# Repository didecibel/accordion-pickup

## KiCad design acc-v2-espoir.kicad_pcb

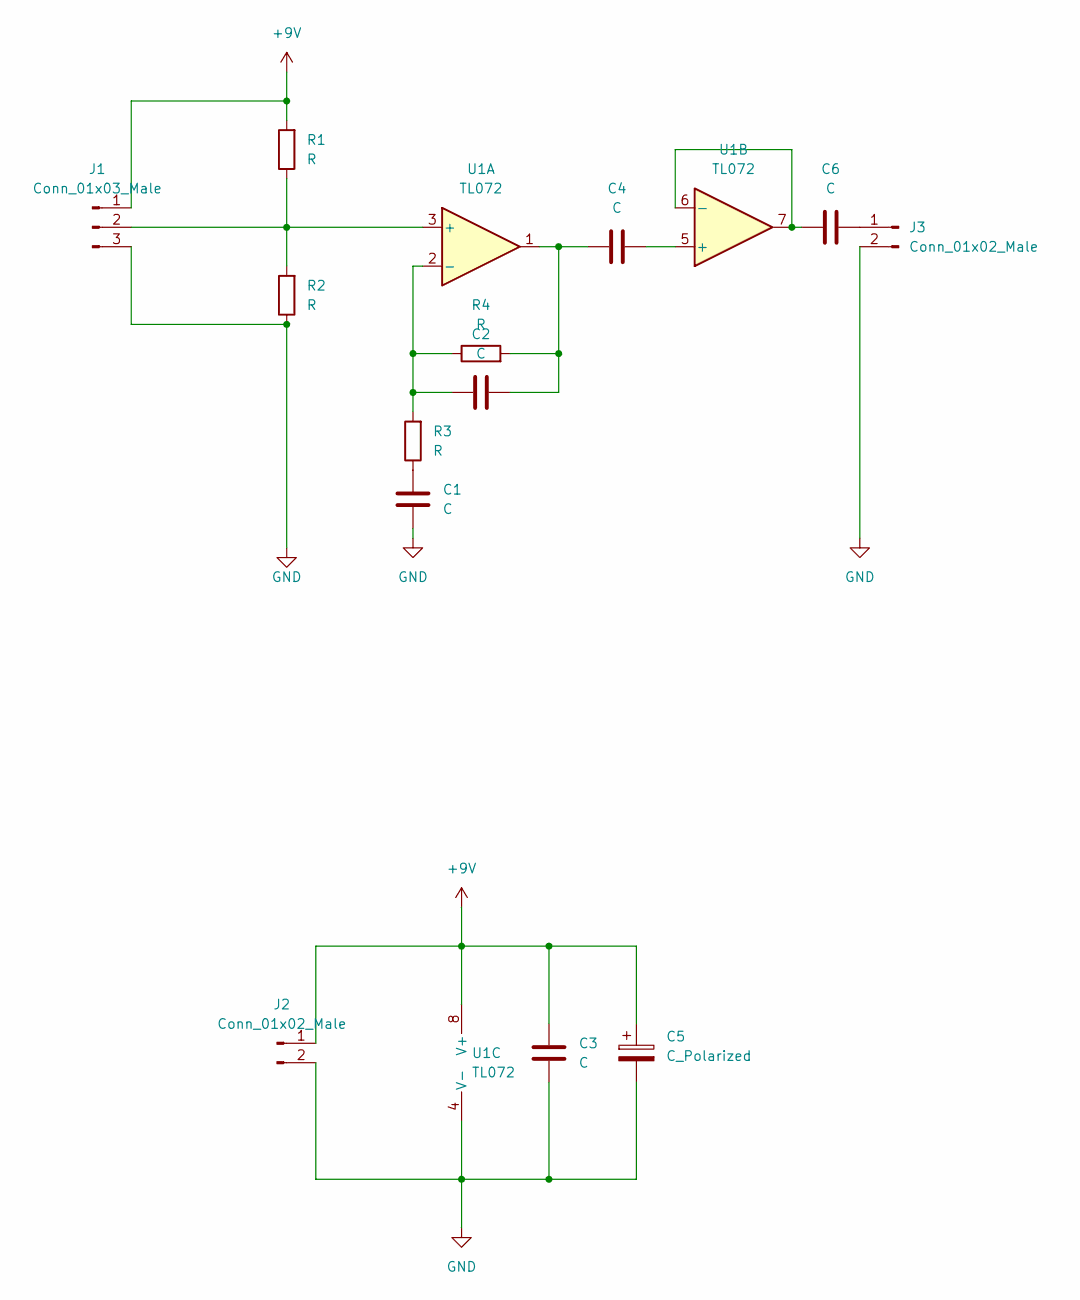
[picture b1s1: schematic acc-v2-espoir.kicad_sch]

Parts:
C1: C; CP_Radial_D8.0mm_P5.00mm
C2, C3, C4, C6: C; C_Disc_D7.5mm_W5.0mm_P10.00mm
C5: C_Polarized; CP_Radial_D8.0mm_P5.00mm
J1: Conn_01x03_Male; FanPinHeader_1x03_P2.54mm_Vertical
J2, J3: Conn_01x02_Male; Molex_SL_171971-0002_1x02_P2.54mm_Vertical
R1, R2, R3, R4: R; R_Axial_DIN0207_L6.3mm_D2.5mm_P7.62mm_Horizontal
U1: TL072; DIP-8_W7.62mm_LongPads

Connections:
+9V: C3.1, C5.1, J1.1, J2.1, R1.2, U1.8 (V+)
GND: C1.1, C3.2, C5.2, J1.3, J2.2, J3.2, R2.1, U1.4 (V-)
unnamed: C1.2, R3.1
unnamed: C2.1, R3.2, R4.1, U1.2 (-)
unnamed: C2.2, C4.1, R4.2, U1.1
unnamed: C4.2, U1.5 (+)
unnamed: C6.1, U1.6 (-), U1.7
unnamed: C6.2, J3.1
unnamed: J1.2, R1.1, R2.2, U1.3 (+)

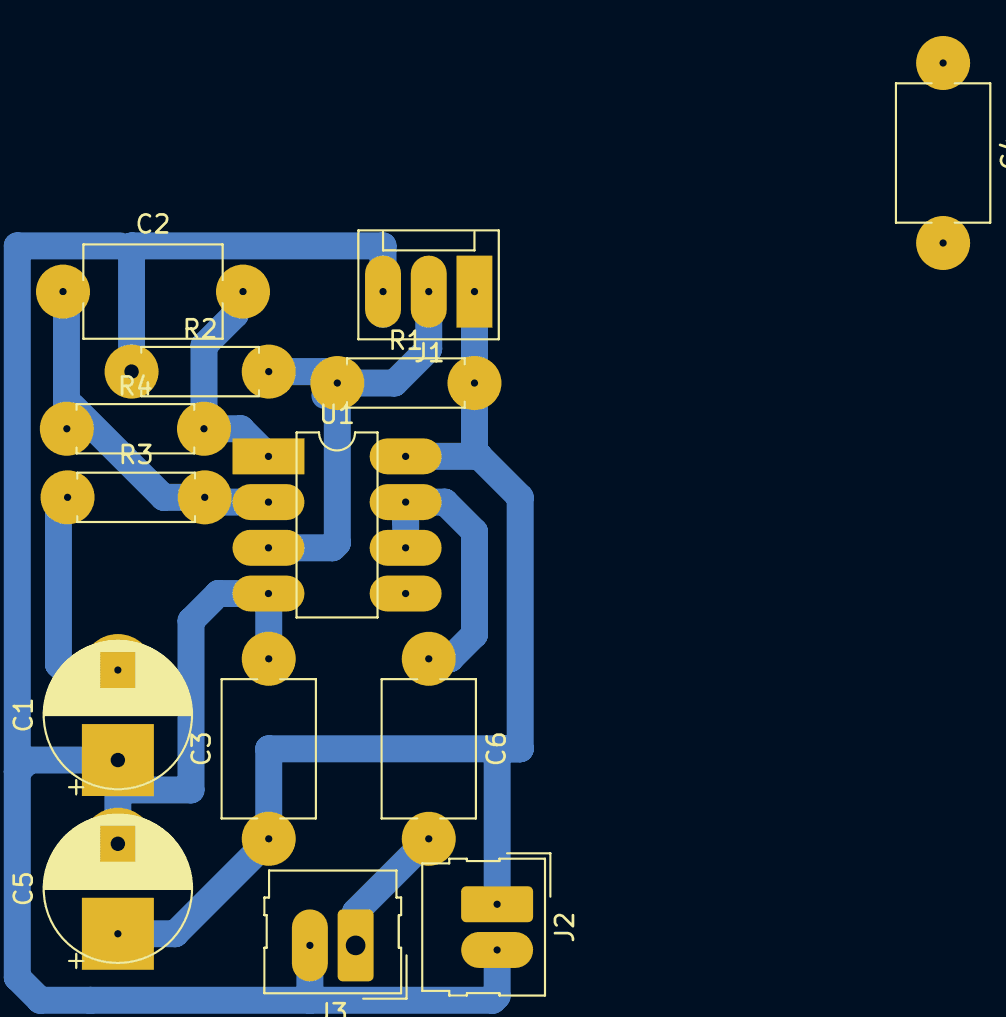
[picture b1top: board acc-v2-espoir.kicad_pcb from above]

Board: 2 copper layers, 14 parts (0 on the bottom side), 9 nets.

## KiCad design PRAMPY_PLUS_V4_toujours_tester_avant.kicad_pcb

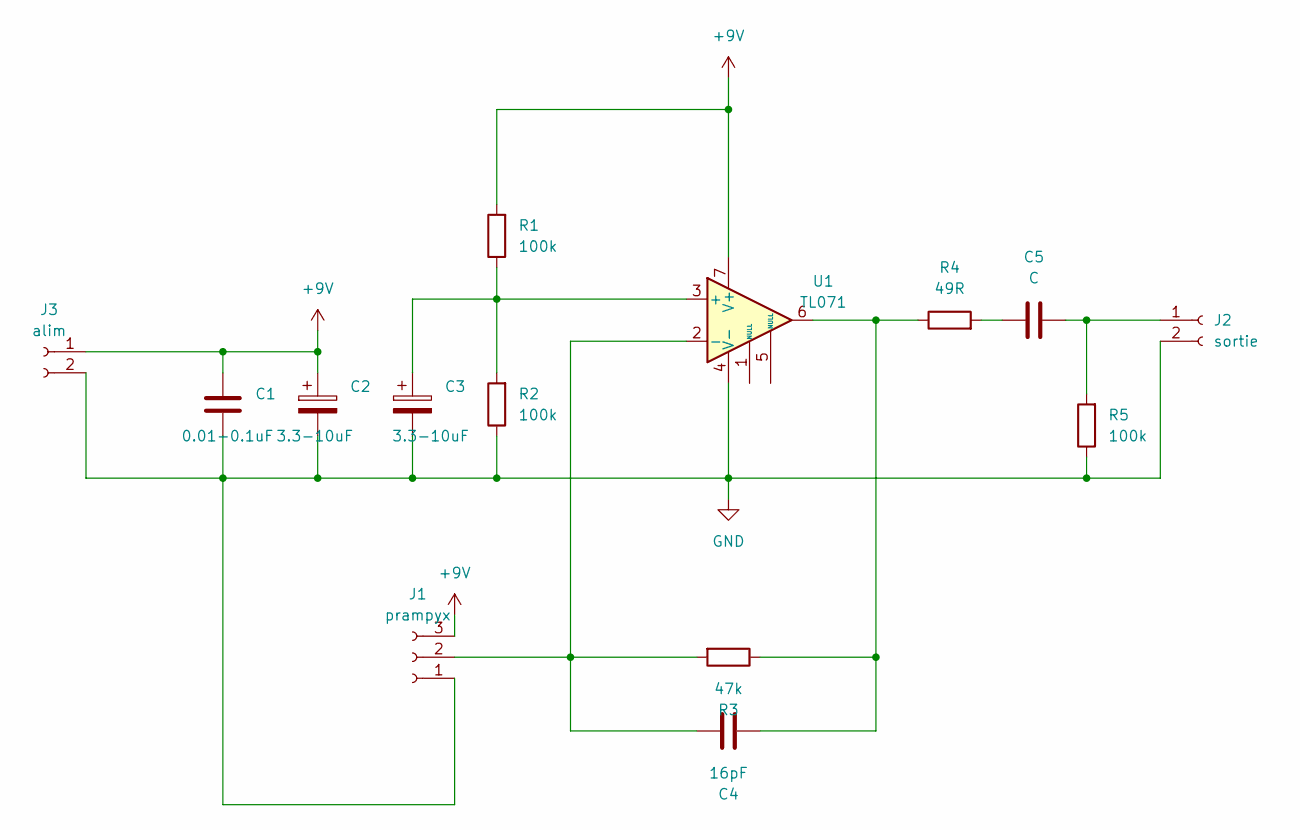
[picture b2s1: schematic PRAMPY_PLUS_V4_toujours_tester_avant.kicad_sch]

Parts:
C1: 0.01-0.1uF; C_Rect_L9.0mm_W3.3mm_P7.50mm_MKT
C2, C3: 3.3-10uF; CP_Radial_D8.0mm_P5.00mm
C4: 16pF; C_Disc_D7.5mm_W2.5mm_P5.00mm
C5: C; C_Rect_L9.0mm_W5.1mm_P7.50mm_MKT
J1: prampyx; FanPinHeader_1x03_P2.54mm_Vertical
J2: sortie; JWT_A3963_1x02_P3.96mm_Vertical
J3: alim; JWT_A3963_1x02_P3.96mm_Vertical
R1, R2, R5: 100k; R_Axial_DIN0207_L6.3mm_D2.5mm_P7.62mm_Horizontal
R3: 47k; R_Axial_DIN0207_L6.3mm_D2.5mm_P7.62mm_Horizontal
R4: 49R; R_Axial_DIN0207_L6.3mm_D2.5mm_P7.62mm_Horizontal
U1: TL071; DIP-8_W7.62mm_LongPads

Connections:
+9V: C1.1, C2.1, J1.3, J3.1, R1.2, U1.7 (V+)
GND: C1.2, C2.2, C3.2, J1.1, J2.2, J3.2, R2.1, R5.1, U1.4 (V-)
unnamed: C3.1, R1.1, R2.2, U1.3 (+)
unnamed: C4.1, R3.1, R4.1, U1.6
unnamed: C4.2, J1.2, R3.2, U1.2 (-)
unnamed: C5.1, R4.2
unnamed: C5.2, J2.1, R5.2

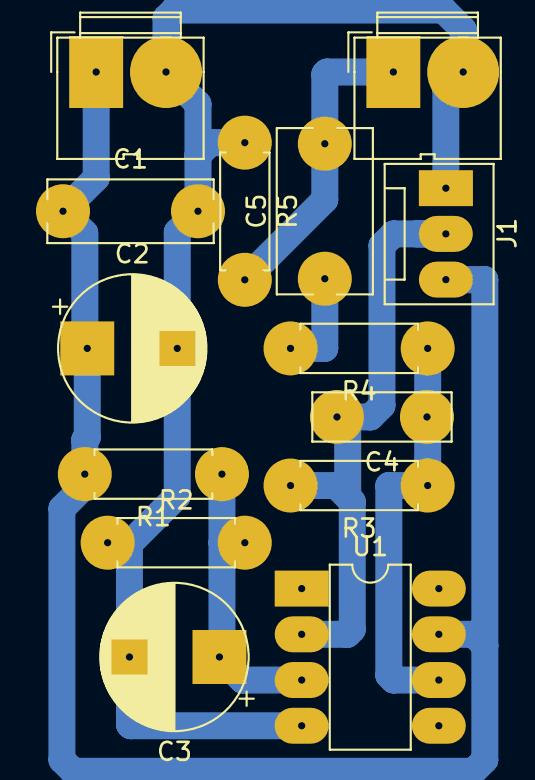
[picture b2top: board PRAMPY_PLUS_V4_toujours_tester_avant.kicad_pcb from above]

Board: 2 copper layers, 14 parts (0 on the bottom side), 7 nets.

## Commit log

2025-07-12 README.md
